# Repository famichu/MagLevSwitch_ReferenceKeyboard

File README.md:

# MagLev Switch Reference Keyboard

## Summary
This keyboard is a reference keyboard for using the MagLev switch, which has linear-output Hall effect sensors and magnetic levitation switches.

## Features
- A 28-switches keyboard for the left hand
- Uses 4 MagLev switches for the WASD keys
- Able to read the depth of the MagLev switches
- Built-in OLED displaying MagLev switch depth graphs

## BOM
### Main PCB
- Main PCB x1
- Kailh Switch Socket x24
- Cherry MX compatible switch x24
- MagLev Switch MX x4
- Stabilizer(2U) x2
- Incremental rotary encoder(PEC12R series of compatible) x1
- RP2040 x1
- Other small devices(refer to the schematic)

### Flex-PCB with OLED
- Flex-PCB x1
- OLED SSD1366 x1
- Other small devices(please refer the schematic)

###  Shell
- Top case(3D printed) x1
- Top plate(3D printed) x1
- knob(3D printed) x1
- Bottom case(3D printed) x1
- Stand(3D printed) x2
- Rubber foot(25mmx8mm oval) x2
- Bottom switch cap(3D printed) x1
- Screw M2x5mm x4
- Screw M2x8mm x4
- Insert nut M2x3mm(OD3.5mm) x8
- Cherry MX compatible keycap x28

## 3D Printing
Use FFF 3D printers to print shell parts. 

## PCB
I had manufactured at JLCPCB. The main PCB in this repository has an LCSC number as well.
This allows you to order the PCBA without selecting individual devices.

## Assembly
- 1. Solder all devices.
    
- 2. Insert switches through a top plate.

- 3. Place the bottom switch cap onto the bottom case (Insert nuts into holes on the bottom plate if you print it by yourself.).

- 4. Fix the PCB with screws.

- 5. Insert an OLED module with a flex PCB into the top case (Insert nuts into holes on the top plate if you print it by yourself).

- 6. Connect the flex-PCB with the main PCB.

- 7. Close the top and bottom cases with screws.

- 8. Stick rubber feets.

- 9. Install keycaps and a knob.

- 10. Finish!

# Directory configuration
- bin: Binary of the firmware
- pcb: Schematics & PCB artworks
    - libs: PCB libraries
    - Reference_Keyboard: Main PCB
    - SSD1366_FFC_Adapter: Flex-PCB with OLED
- shell: 3D models for FFF printer
- src: Source codes of the firmware

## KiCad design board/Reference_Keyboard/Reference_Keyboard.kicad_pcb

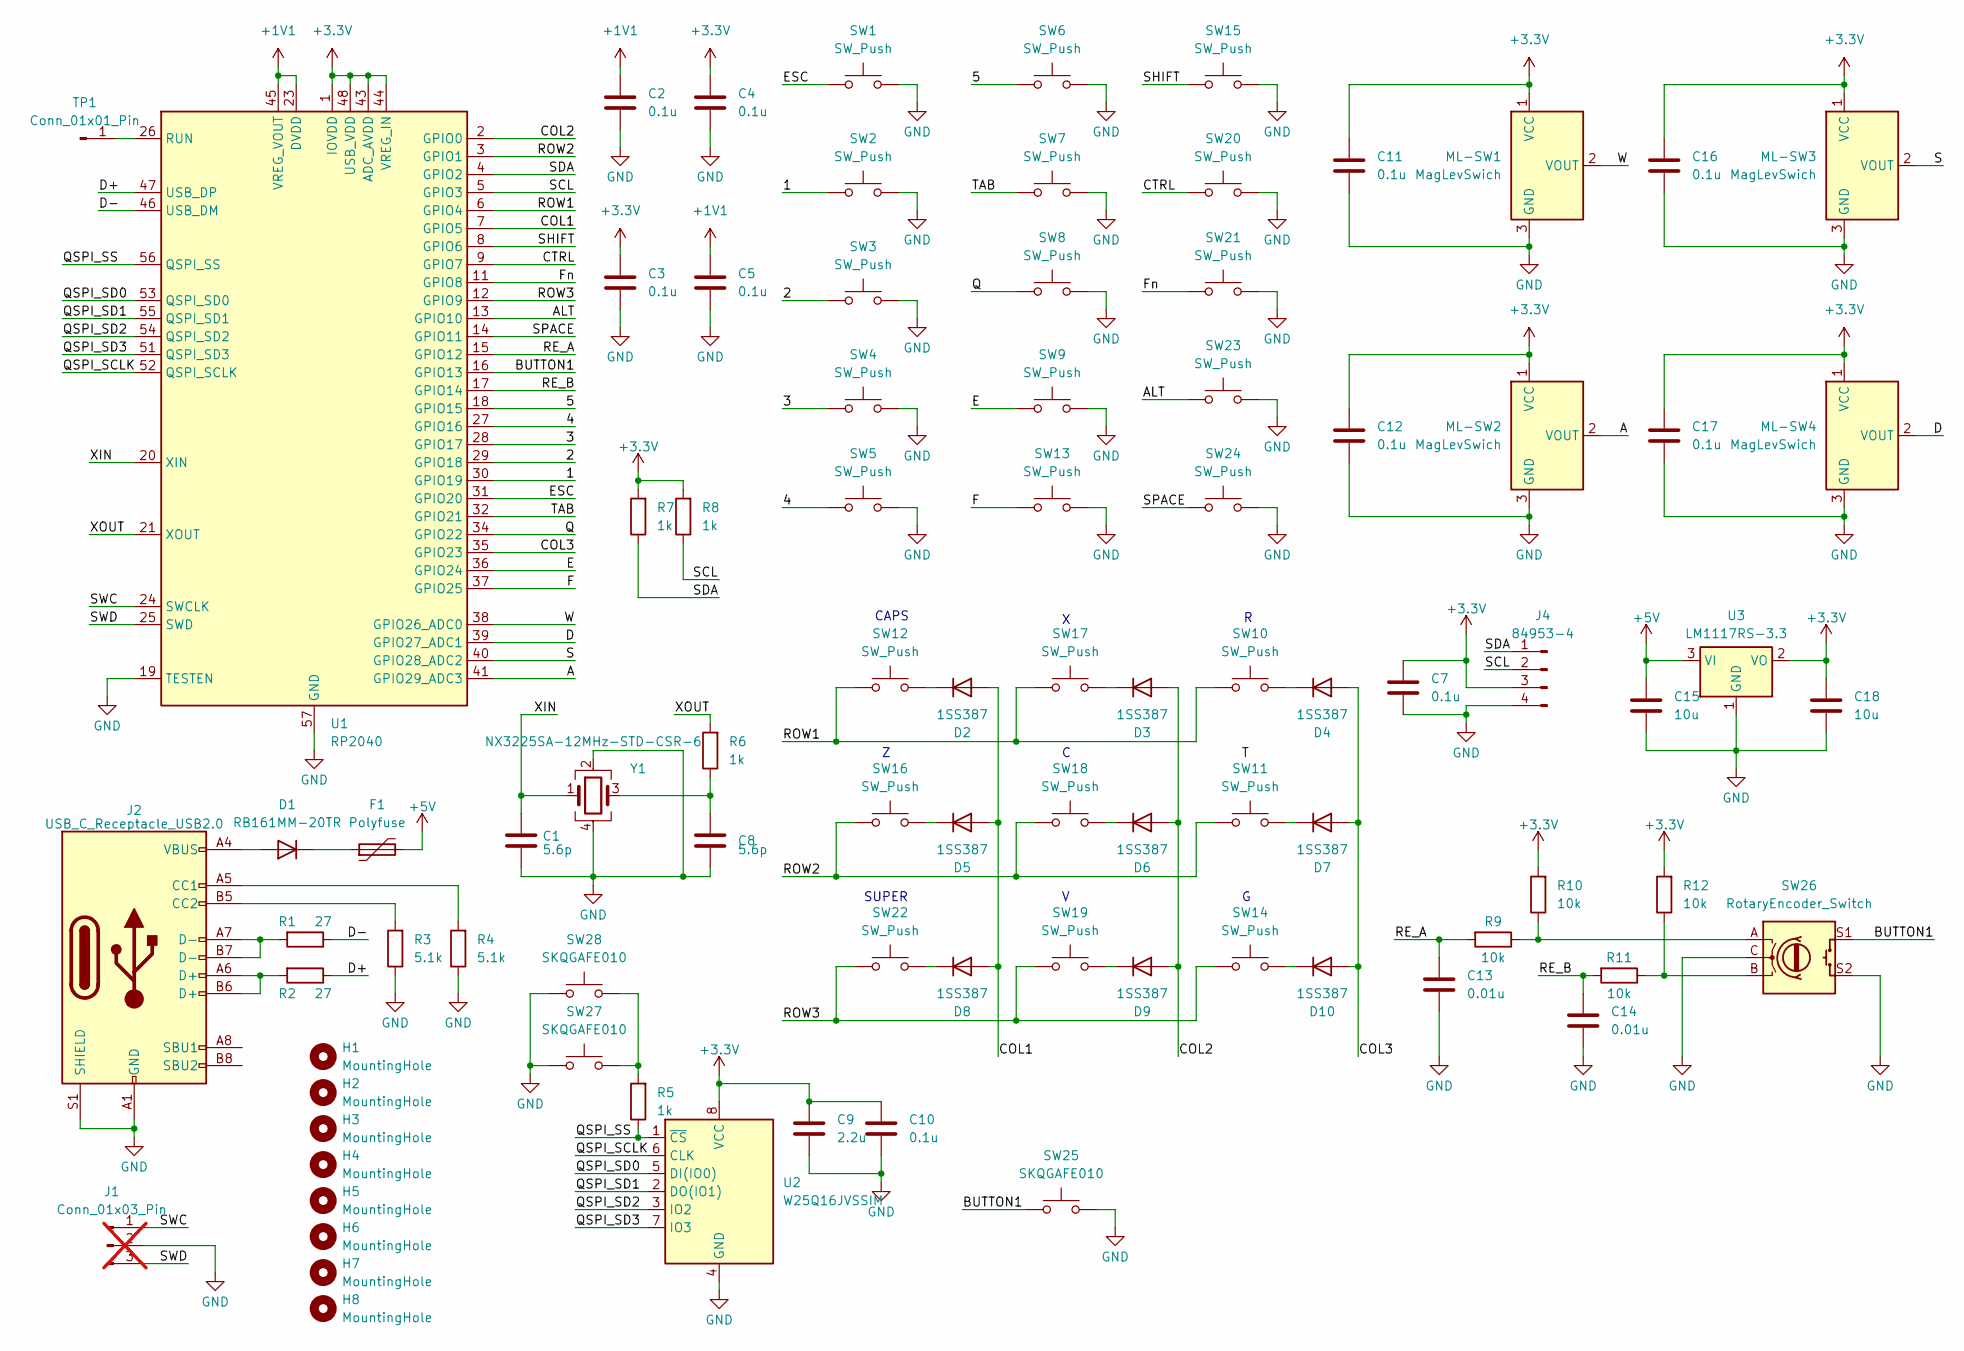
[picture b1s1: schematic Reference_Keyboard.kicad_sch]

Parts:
C1, C8: 5.6p; C_0603_1608Metric
C2, C3, C4, C5, C7, C10, C11, C12, C16, C17: 0.1u; C_0603_1608Metric
C9: 2.2u; C_0603_1608Metric
C13, C14: 0.01u; C_0603_1608Metric
C15, C18: 10u; C_0603_1608Metric
D1: RB161MM-20TR; D_SOD-123F; LCSC C123070
D2, D3, D4, D5, D6, D7, D8, D9, D10: 1SS387; D_SOD-523; LCSC C146426
F1: Polyfuse; Fuse_0805_2012Metric
H1, H2, H3, H4, H5, H6, H7, H8: MountingHole; MountingHole_2.2mm_M2
J1: Conn_01x03_Pin; PinHeader_1x03_P2.54mm_Vertical; not fitted
J2: USB_C_Receptacle_USB2.0; USB_C_Receptacle_HRO_TYPE-C-31-M-12; LCSC C165948
J4: 84953-4; TE_84953-4_1x04-1MP_P1.0mm_Horizontal; LCSC C590896
ML-SW1, ML-SW2, ML-SW3, ML-SW4: MagLevSwich; MagLevSwitch_Up
R1, R2: 27; R_0603_1608Metric
R3, R4: 5.1k; R_0603_1608Metric
R5, R6, R7, R8: 1k; R_0603_1608Metric
R9, R10, R11, R12: 10k; R_0603_1608Metric
SW1, SW2, SW3, SW4, SW5, SW6, SW8, SW9, SW10, SW11, SW13, SW14, SW16, SW17, SW18, SW19, SW21, SW22, SW23: SW_Push; MX-Hotswap-1U
SW7: SW_Push; MX-Hotswap-1.5U
SW12: SW_Push; MX-Hotswap-1.75U
SW15, SW24: SW_Push; MX-Hotswap-2.25U
SW20: SW_Push; MX-Hotswap-1.25U
SW25, SW27, SW28: SKQGAFE010; SW_SPST_SKQG_WithStem; LCSC C202424
SW26: RotaryEncoder_Switch; RotaryEncoder_Alps_EC11E-Switch_Vertical_H20mm
TP1: Conn_01x01_Pin; TestPoint_Pad_D1.5mm
U1: RP2040; QFN-56-1EP_7x7mm_P0.4mm_EP3.2x3.2mm; LCSC C2040
U2: W25Q16JVSSIM; SOIC-8_5.23x5.23mm_P1.27mm; LCSC C82317
U3: LM1117RS-3.3; TO-252-3_TabPin2; LCSC C126023
Y1: NX3225SA-12MHz-STD-CSR-6; Crystal_SMD_3225-4Pin_3.2x2.5mm; LCSC C481400

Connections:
+1V1: C2.1, C5.1, U1.23 (DVDD), U1.45 (VREG_VOUT), U1.50 (DVDD)
+3.3V: C3.1, C4.1, C7.1, C9.1, C10.1, C11.1, C12.1, C16.1, C17.1, C18.1, J4.3, ML-SW1.1 (VCC), ML-SW2.1 (VCC), ML-SW3.1 (VCC), ML-SW4.1 (VCC), R7.2, R8.2, R10.2, R12.2, U1.1 (IOVDD), U1.10 (IOVDD), U1.22 (IOVDD), U1.33 (IOVDD), U1.42 (IOVDD), U1.43 (ADC_AVDD), U1.44 (VREG_IN), U1.48 (USB_VDD), U1.49 (IOVDD), U2.8 (VCC), U3.2 (VO)
+5V: C15.1, F1.2, U3.3 (VI)
/1: SW2.1, U1.30 (GPIO19)
/2: SW3.1, U1.29 (GPIO18)
/3: SW4.1, U1.28 (GPIO17)
/4: SW5.1, U1.27 (GPIO16)
/5: SW6.1, U1.18 (GPIO15)
/A: ML-SW2.2 (VOUT), U1.41 (GPIO29_ADC3)
/ALT: SW23.1, U1.13 (GPIO10)
/BUTTON1: SW25.1, SW26.S1, U1.16 (GPIO13)
/COL1: D2.2 (A), D5.2 (A), D8.2 (A), U1.7 (GPIO5)
/COL2: D3.2 (A), D6.2 (A), D9.2 (A), U1.2 (GPIO0)
/COL3: D4.2 (A), D7.2 (A), D10.2 (A), U1.35 (GPIO23)
/CTRL: SW20.1, U1.9 (GPIO7)
/D: ML-SW4.2 (VOUT), U1.39 (GPIO27_ADC1)
/D+: R2.1, U1.47 (USB_DP)
/D-: R1.1, U1.46 (USB_DM)
/E: SW9.1, U1.36 (GPIO24)
/ESC: SW1.1, U1.31 (GPIO20)
/F: SW13.1, U1.37 (GPIO25)
/Fn: SW21.1, U1.11 (GPIO8)
/Q: SW8.1, U1.34 (GPIO22)
/QSPI_SCLK: U1.52 (QSPI_SCLK), U2.6 (CLK)
/QSPI_SD0: U1.53 (QSPI_SD0), U2.5 (DI(IO0))
/QSPI_SD1: U1.55 (QSPI_SD1), U2.2 (DO(IO1))
/QSPI_SD2: U1.54 (QSPI_SD2), U2.3 (IO2)
/QSPI_SD3: U1.51 (QSPI_SD3), U2.7 (IO3)
/QSPI_SS: R5.1, U1.56 (QSPI_SS), U2.1 (~CS)
/RE_A: C13.1, R9.2, U1.15 (GPIO12)
/RE_B: C14.1, R11.2, U1.17 (GPIO14)
/ROW1: SW10.1, SW12.1, SW17.1, U1.6 (GPIO4)
/ROW2: SW11.1, SW16.1, SW18.1, U1.3 (GPIO1)
/ROW3: SW14.1, SW19.1, SW22.1, U1.12 (GPIO9)
/S: ML-SW3.2 (VOUT), U1.40 (GPIO28_ADC2)
/SCL: J4.2, R8.1, U1.5 (GPIO3)
/SDA: J4.1, R7.1, U1.4 (GPIO2)
/SHIFT: SW15.1, U1.8 (GPIO6)
/SPACE: SW24.1, U1.14 (GPIO11)
/SWC: J1.1, U1.24 (SWCLK)
/SWD: J1.3, U1.25 (SWD)
/TAB: SW7.1, U1.32 (GPIO21)
/W: ML-SW1.2 (VOUT), U1.38 (GPIO26_ADC0)
/XIN: C1.1, U1.20 (XIN), Y1.1
/XOUT: R6.2, U1.21 (XOUT)
GND: C1.2, C2.2, C3.2, C4.2, C5.2, C7.2, C8.2, C9.2, C10.2, C11.2, C12.2, C13.2, C14.2, C15.2, C16.2, C17.2, C18.2, J1.2, J2.A1 (GND), J2.A12 (GND), J2.B1 (GND), J2.B12 (GND), J2.S1 (SHIELD), J4.4, ML-SW1.3 (GND), ML-SW2.3 (GND), ML-SW3.3 (GND), ML-SW4.3 (GND), R3.1, R4.1, SW1.2, SW2.2, SW3.2, SW4.2, SW5.2, SW6.2, SW7.2, SW8.2, SW9.2, SW13.2, SW15.2, SW20.2, SW21.2, SW23.2, SW24.2, SW25.2, SW26.C, SW26.S2, SW27.1, SW28.1, U1.19 (TESTEN), U1.57 (GND), U2.4 (GND), U3.1 (GND), Y1.2, Y1.4
unnamed: C8.1, R6.1, Y1.3
unnamed: D1.2 (A), J2.A4 (VBUS), J2.A9 (VBUS), J2.B4 (VBUS), J2.B9 (VBUS)
unnamed: D1.1 (K), F1.1
unnamed: D2.1 (K), SW12.2
unnamed: D3.1 (K), SW17.2
unnamed: D4.1 (K), SW10.2
unnamed: D5.1 (K), SW16.2
unnamed: D6.1 (K), SW18.2
unnamed: D7.1 (K), SW11.2
unnamed: D8.1 (K), SW22.2
unnamed: D9.1 (K), SW19.2
unnamed: D10.1 (K), SW14.2
unnamed: J2.A5 (CC1), R4.2
unnamed: J2.B5 (CC2), R3.2
unnamed: J2.A6 (D+), J2.B6 (D+), R2.2
unnamed: J2.A7 (D-), J2.B7 (D-), R1.2
unnamed: R5.2, SW27.2, SW28.2
unnamed: R9.1, R10.1, SW26.A
unnamed: R11.1, R12.1, SW26.B
unnamed: TP1.1, U1.26 (RUN)

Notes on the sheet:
SUPER
CAPS

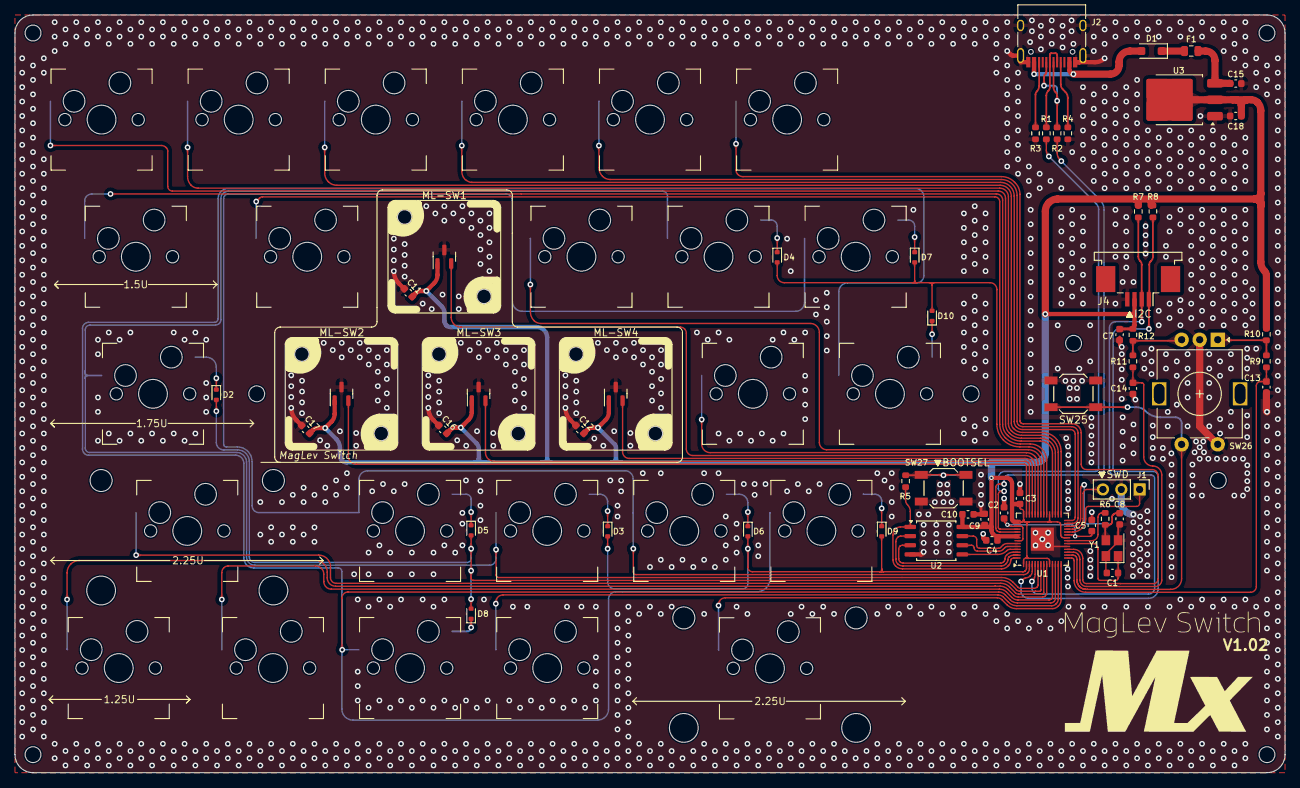
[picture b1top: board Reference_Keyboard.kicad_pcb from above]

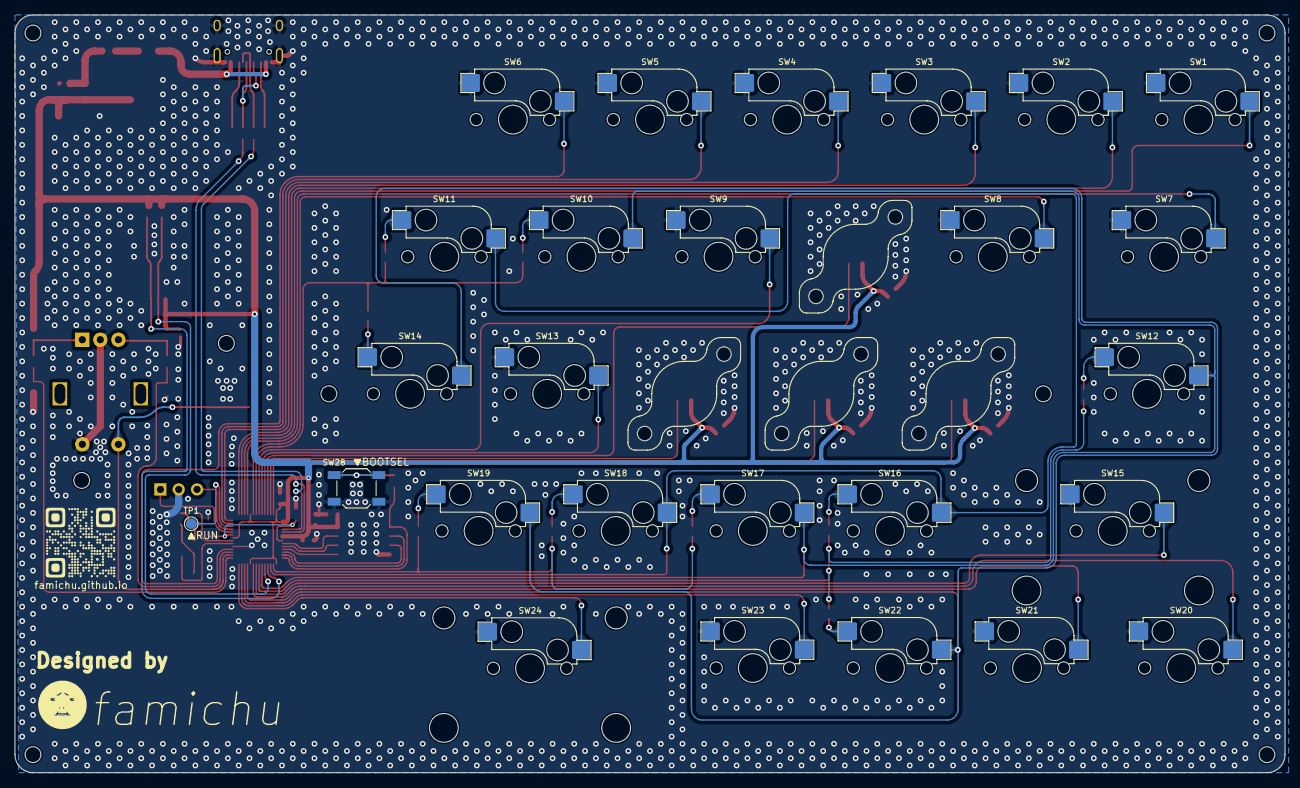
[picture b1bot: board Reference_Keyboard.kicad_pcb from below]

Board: 2 copper layers, 176.0 x 105.0 mm, 88 parts (2 on the bottom side), 66 nets.

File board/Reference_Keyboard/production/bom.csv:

Designator,Footprint,Quantity,Value,LCSC Part #
"C1, C8",0603,2,5.6p,
"C10, C11, C12, C16, C17, C2, C3, C4, C5, C7",0603,10,0.1u,
"C13, C14",0603,2,0.01u,
"C15, C18",0603,2,10u,
C9,0603,1,2.2u,
D1,D_SOD-123F,1,RB161MM-20TR,C123070
"D10, D2, D3, D4, D5, D6, D7, D8, D9",D_SOD-523,9,1SS387,C146426
F1,0805,1,Polyfuse,C524650
"H1, H2, H3, H4, H5, H6, H7, H8",MountingHole_2.2mm_M2,8,MountingHole,
J2,USB_C_Receptacle_HRO_TYPE-C-31-M-12,1,USB_C_Receptacle_USB2.0,C165948
J4,TE_84953-4_1x04-1MP_P1.0mm_Horizontal,1,84953-4,C590896
"ML-SW1, ML-SW2, ML-SW3, ML-SW4",MagLevSwitch_Up,4,MagLevSwich,
"R1, R2",0603,2,27,
"R10, R11, R12, R9",0603,4,10k,
"R3, R4",0603,2,5.1k,
"R5, R6, R7, R8",0603,4,1k,
"SW1, SW10, SW11, SW13, SW14, SW16, SW17, SW18, SW19, SW2, SW21, SW22, SW23, SW3, SW4, SW5, SW6, SW8, SW9",MX-Hotswap-1U,19,SW_Push,
SW12,MX-Hotswap-1.75U,1,SW_Push,
"SW15, SW24",MX-Hotswap-2.25U,2,SW_Push,
SW20,MX-Hotswap-1.25U,1,SW_Push,
"SW25, SW27, SW28",SW_SPST_SKQG_WithStem,3,SKQGAFE010,C202424
SW26,RotaryEncoder_Alps_EC11E-Switch_Vertical_H20mm,1,RotaryEncoder_Switch,
SW7,MX-Hotswap-1.5U,1,SW_Push,
TP1,TestPoint_Pad_D1.5mm,1,Conn_01x01_Pin,
U1,QFN-56-1EP_7x7mm_P0.4mm_EP3.2x3.2mm,1,RP2040,C2040
U2,SOIC-8_5.23x5.23mm_P1.27mm,1,W25Q16JVSSIM,C82317
U3,TO-252-3_TabPin2,1,LM1117RS-3.3,C126023
Y1,Crystal_SMD_3225-4Pin_3.2x2.5mm,1,NX3225SA-12MHz-STD-CSR-6,C481400

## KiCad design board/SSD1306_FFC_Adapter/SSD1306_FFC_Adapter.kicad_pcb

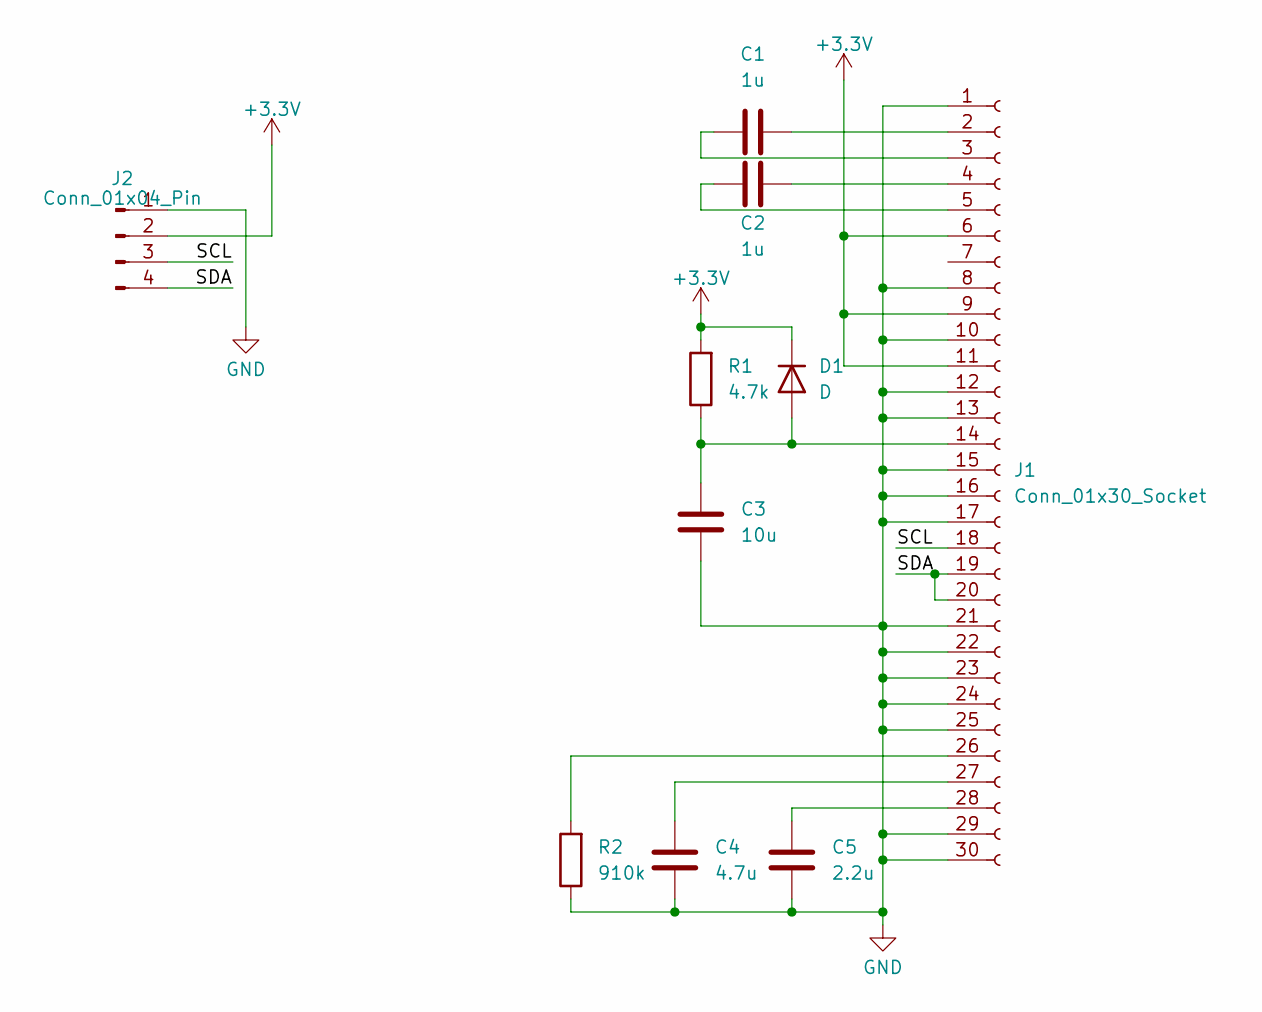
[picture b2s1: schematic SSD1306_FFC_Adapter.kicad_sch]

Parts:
C1, C2: 1u; C_0603_1608Metric
C3: 10u; C_0603_1608Metric
C4: 4.7u; C_0603_1608Metric
C5: 2.2u; C_0603_1608Metric
D1: D; D_0603_1608Metric
J1: Conn_01x30_Socket; OLED-128O064D
J2: Conn_01x04_Pin; FFC-FPC_1mm_1x04
R1: 4.7k; R_0603_1608Metric
R2: 910k; R_0603_1608Metric

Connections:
+3.3V: D1.1 (K), J1.6, J1.9, J1.11, J2.2, R1.2
/SCL: J1.18, J2.3
/SDA: J1.19, J1.20, J2.4
GND: C3.1, C4.1, C5.1, J1.1, J1.8, J1.10, J1.12, J1.13, J1.15, J1.16, J1.17, J1.21, J1.22, J1.23, J1.24, J1.25, J1.29, J1.30, J2.1, R2.1
unnamed: C3.2, D1.2 (A), J1.14, R1.1
unnamed: C1.2, J1.2
unnamed: C1.1, J1.3
unnamed: C2.2, J1.4
unnamed: C2.1, J1.5
unnamed: J1.26, R2.2
unnamed: C4.2, J1.27
unnamed: C5.2, J1.28

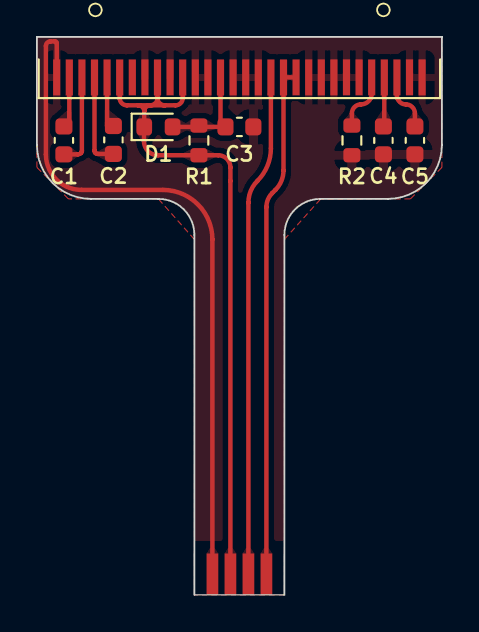
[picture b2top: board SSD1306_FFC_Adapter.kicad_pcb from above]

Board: 2 copper layers, 22.5 x 31.0 mm, 10 parts (0 on the bottom side), 12 nets.

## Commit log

2024-04-29 First version
    First version(no outer shells).
2024-05-15 Add thresholds adjust function
2024-05-15 Add BarGraph
2024-05-16 rollback debug display and minor fixes
2024-05-16 Add the adjustable actuation point and the release point of switches
2024-05-19 Add the thresholds memory function
2024-05-23 Fix quick release function
2024-05-23 Change the thresholds adjustment method
2024-05-23 Change works in middle depth
2024-05-24 Add 3d models
2024-06-01 Bug fix for the Fn key
2024-07-13 add firmware and PCB for hardware v1.01
2024-08-11 refactor classes and structure of the save datas
2024-08-25 Change thresholds for the rapid triger
2024-08-25 Add 3d models for hardweare v1.01
2024-10-06 Add an option for disable thresholds
2024-10-06 Add a current protection circuit
2024-10-07 Fix typo & change version on the logo
2024-11-12 Move logo array to the MaglevSwitch_Board.h
2024-11-24 Update 3d models
2024-12-19 change FN key code
2024-12-19 change the poly-fuse
2025-03-28 Update readme, directories, and 3d models
2025-03-28 fix readme
2025-03-29 fix typo
